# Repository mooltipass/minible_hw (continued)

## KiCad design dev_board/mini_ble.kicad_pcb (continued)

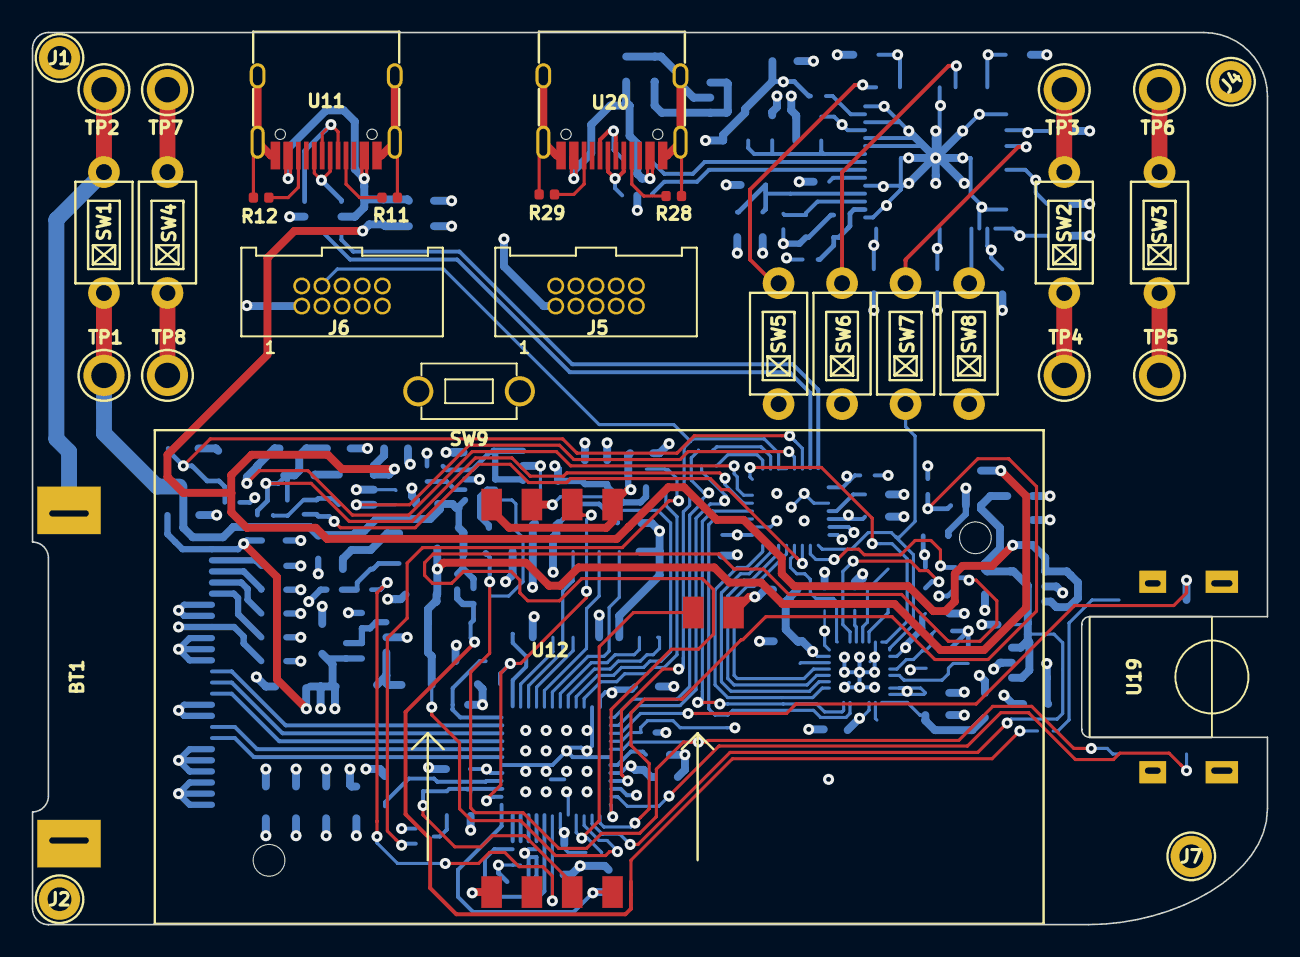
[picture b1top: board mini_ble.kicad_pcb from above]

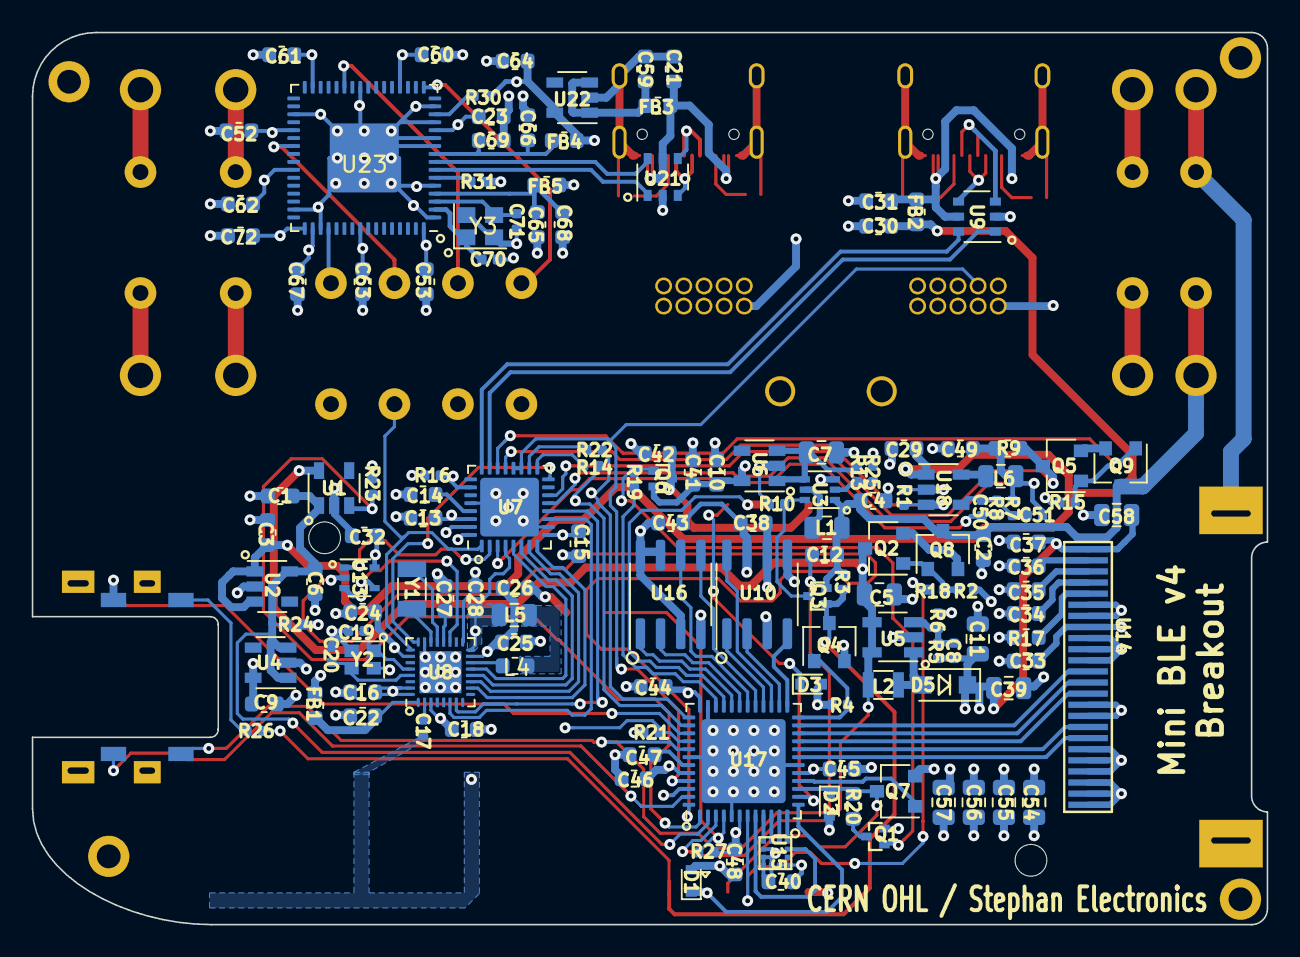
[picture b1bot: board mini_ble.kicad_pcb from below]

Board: 4 copper layers, 77.8 x 56.2 mm, 176 parts (144 on the bottom side), 128 nets.

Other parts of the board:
J1, J2, J4, J7: FIX_M1.4

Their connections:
GND: J1.1, J2.1, J4.1, J7.1; also elsewhere on the board
